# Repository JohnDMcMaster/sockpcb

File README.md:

# sockext

Chip socket extension cable adapters.
They are primarily intended to be high quality fixtures for invasive chip analysis such as microprobing, laser fault injection, and EM SCA.

Example: BP Microsystems programmers are high quality but physically large.
Unfortunately this large size precludes it from being used to read out a chip on my probe station.
Solution: extend the socket from the programmer via ribbon cable to an adapter board on the probe station (dipext-pin + dipext-sock + cable).

Projects:
  * dipext-sock: converts an IDC connector to a ZIF40 socket. Also adds patch connections
  * dipext-pin: converts DIP40 pins into an IDC connector. Also adds patch connections
  * dipext-pin-r: like above but flips pins for backside analysis
    * WARNING: not updated for new pin order
  * dipspy: patch a chip similar to dipext-sock + dipext-pin w/o cables and such
    * FIXME: needs rev to use SMD to make solder easier

IMPORTANT: pin order was swapped at this rev to match crimp connectors:
  * dipext-sock_r3
  * dipext-pin_r6
  * WARNING: dipext-pin-r_r1 is not compatible / updated yet

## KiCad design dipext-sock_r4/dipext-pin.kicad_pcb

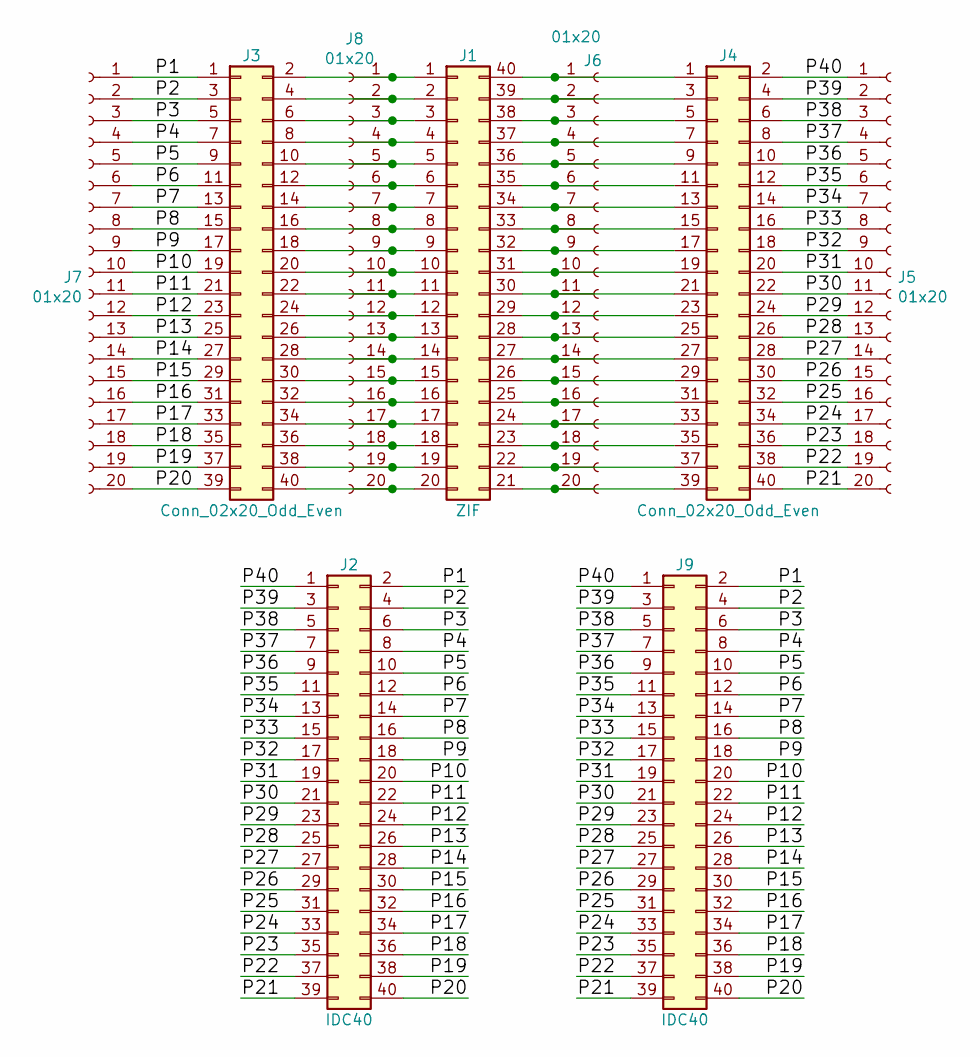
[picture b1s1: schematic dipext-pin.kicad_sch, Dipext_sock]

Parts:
J1: ZIF; mydip40
J2, J9: IDC40; IDC-Header_2x20_P2.54mm_Latch_Vertical
J3, J4: Conn_02x20_Odd_Even; Pin_Header_Straight_2x20_Pitch2.54mm
J5, J6, J7, J8: 01x20; PinHeader_1x20_P2.54mm_Vertical

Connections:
/P1: J2.2, J3.1, J7.1, J9.2
/P2: J2.4, J3.3, J7.2, J9.4
/P3: J2.6, J3.5, J7.3, J9.6
/P4: J2.8, J3.7, J7.4, J9.8
/P5: J2.10, J3.9, J7.5, J9.10
/P6: J2.12, J3.11, J7.6, J9.12
/P7: J2.14, J3.13, J7.7, J9.14
/P8: J2.16, J3.15, J7.8, J9.16
/P9: J2.18, J3.17, J7.9, J9.18
/P10: J2.20, J3.19, J7.10, J9.20
/P11: J2.22, J3.21, J7.11, J9.22
/P12: J2.24, J3.23, J7.12, J9.24
/P13: J2.26, J3.25, J7.13, J9.26
/P14: J2.28, J3.27, J7.14, J9.28
/P15: J2.30, J3.29, J7.15, J9.30
/P16: J2.32, J3.31, J7.16, J9.32
/P17: J2.34, J3.33, J7.17, J9.34
/P18: J2.36, J3.35, J7.18, J9.36
/P19: J2.38, J3.37, J7.19, J9.38
/P20: J2.40, J3.39, J7.20, J9.40
/P21: J2.39, J4.40, J5.20, J9.39
/P22: J2.37, J4.38, J5.19, J9.37
/P23: J2.35, J4.36, J5.18, J9.35
/P24: J2.33, J4.34, J5.17, J9.33
/P25: J2.31, J4.32, J5.16, J9.31
/P26: J2.29, J4.30, J5.15, J9.29
/P27: J2.27, J4.28, J5.14, J9.27
/P28: J2.25, J4.26, J5.13, J9.25
/P29: J2.23, J4.24, J5.12, J9.23
/P30: J2.21, J4.22, J5.11, J9.21
/P31: J2.19, J4.20, J5.10, J9.19
/P32: J2.17, J4.18, J5.9, J9.17
/P33: J2.15, J4.16, J5.8, J9.15
/P34: J2.13, J4.14, J5.7, J9.13
/P35: J2.11, J4.12, J5.6, J9.11
/P36: J2.9, J4.10, J5.5, J9.9
/P37: J2.7, J4.8, J5.4, J9.7
/P38: J2.5, J4.6, J5.3, J9.5
/P39: J2.3, J4.4, J5.2, J9.3
/P40: J2.1, J4.2, J5.1, J9.1
unnamed: J1.1, J3.2, J8.1
unnamed: J1.2, J3.4, J8.2
unnamed: J1.3, J3.6, J8.3
unnamed: J1.4, J3.8, J8.4
unnamed: J1.5, J3.10, J8.5
unnamed: J1.6, J3.12, J8.6
unnamed: J1.7, J3.14, J8.7
unnamed: J1.8, J3.16, J8.8
unnamed: J1.9, J3.18, J8.9
unnamed: J1.10, J3.20, J8.10
unnamed: J1.11, J3.22, J8.11
unnamed: J1.12, J3.24, J8.12
unnamed: J1.13, J3.26, J8.13
unnamed: J1.14, J3.28, J8.14
unnamed: J1.15, J3.30, J8.15
unnamed: J1.16, J3.32, J8.16
unnamed: J1.17, J3.34, J8.17
unnamed: J1.18, J3.36, J8.18
unnamed: J1.19, J3.38, J8.19
unnamed: J1.20, J3.40, J8.20
unnamed: J1.21, J4.39, J6.20
unnamed: J1.22, J4.37, J6.19
unnamed: J1.23, J4.35, J6.18
unnamed: J1.24, J4.33, J6.17
unnamed: J1.25, J4.31, J6.16
unnamed: J1.26, J4.29, J6.15
unnamed: J1.27, J4.27, J6.14
unnamed: J1.28, J4.25, J6.13
unnamed: J1.29, J4.23, J6.12
unnamed: J1.30, J4.21, J6.11
unnamed: J1.31, J4.19, J6.10
unnamed: J1.32, J4.17, J6.9
unnamed: J1.33, J4.15, J6.8
unnamed: J1.34, J4.13, J6.7
unnamed: J1.35, J4.11, J6.6
unnamed: J1.36, J4.9, J6.5
unnamed: J1.37, J4.7, J6.4
unnamed: J1.38, J4.5, J6.3
unnamed: J1.39, J4.3, J6.2
unnamed: J1.40, J4.1, J6.1

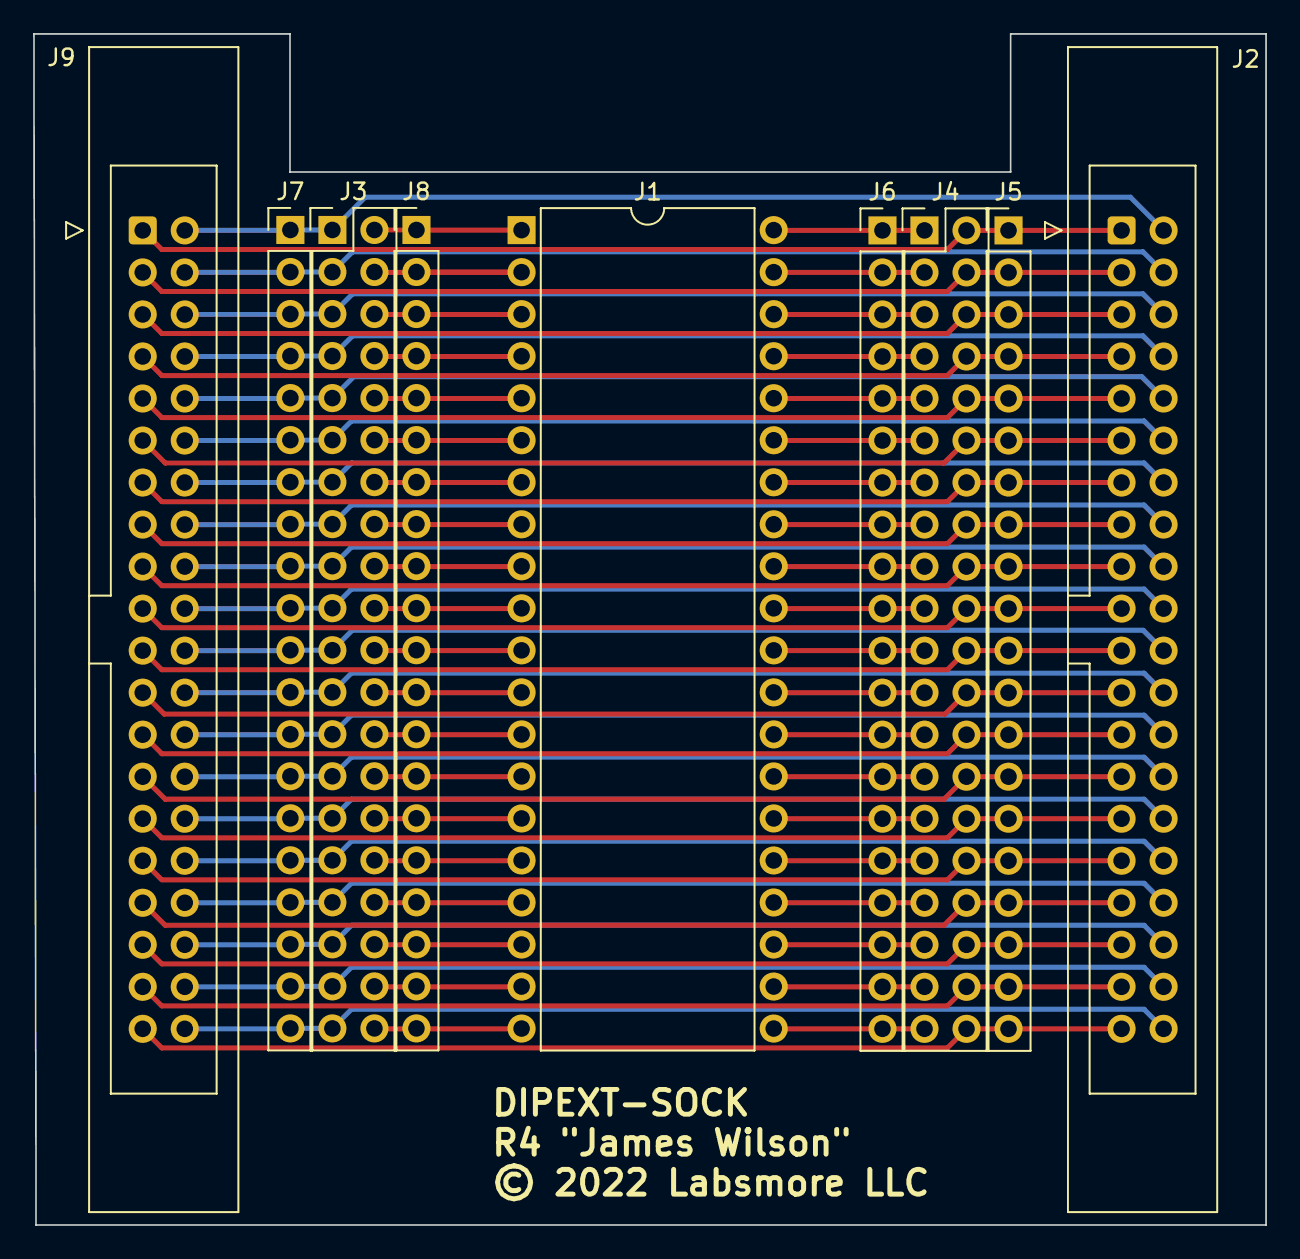
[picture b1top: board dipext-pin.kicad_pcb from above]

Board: 2 copper layers, 74.5 x 72.0 mm, 9 parts (0 on the bottom side), 80 nets.

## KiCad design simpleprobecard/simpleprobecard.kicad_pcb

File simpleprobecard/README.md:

# Simple microprobing breakout thing for 0.5mm wide probes
Hole is parametric, can be cut to any size.
Mounting points are on a standard 1" grid.

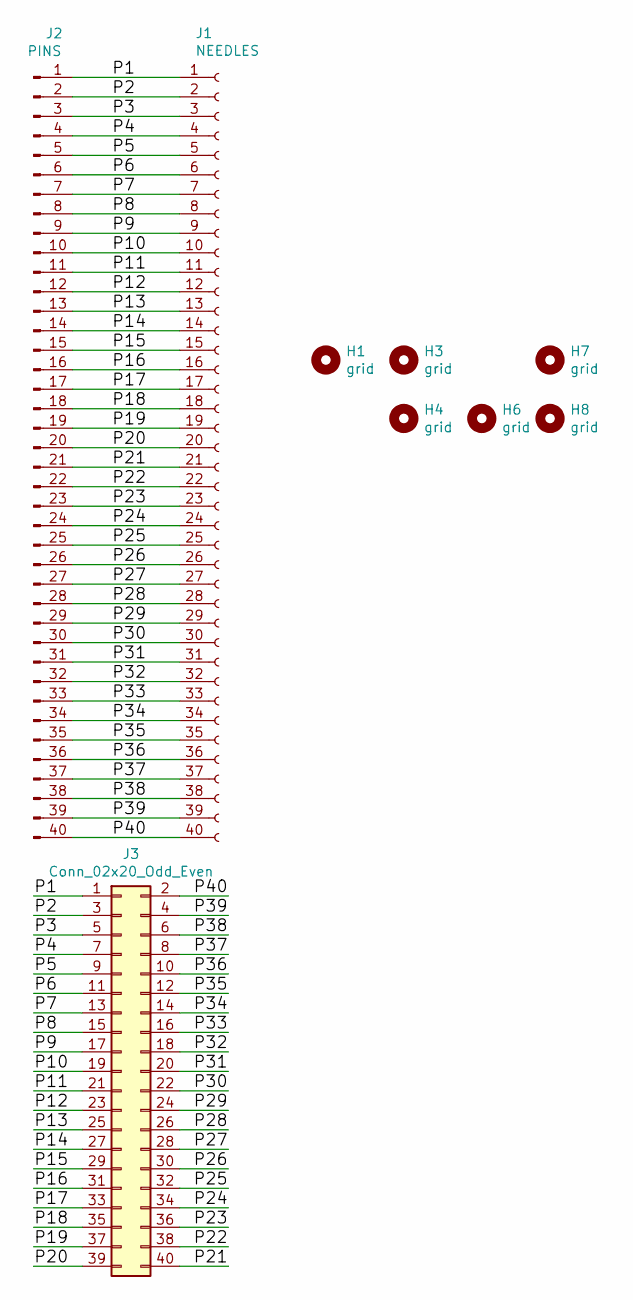
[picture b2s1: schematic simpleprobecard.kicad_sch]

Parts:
H1, H3, H4, H6, H7, H8: grid; MountingHole_4.3mm_M4_Pad_Via
J1: NEEDLES; Pin
J2: PINS; IDC-Header_2x20_P2.54mm_Latch_Vertical
J3: Conn_02x20_Odd_Even; IDC-Header_2x20_P2.54mm_Latch_Vertical

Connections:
/P1: J1.1, J2.1, J3.1
/P2: J1.2, J2.2, J3.3
/P3: J1.3, J2.3, J3.5
/P4: J1.4, J2.4, J3.7
/P5: J1.5, J2.5, J3.9
/P6: J1.6, J2.6, J3.11
/P7: J1.7, J2.7, J3.13
/P8: J1.8, J2.8, J3.15
/P9: J1.9, J2.9, J3.17
/P10: J1.10, J2.10, J3.19
/P11: J1.11, J2.11, J3.21
/P12: J1.12, J2.12, J3.23
/P13: J1.13, J2.13, J3.25
/P14: J1.14, J2.14, J3.27
/P15: J1.15, J2.15, J3.29
/P16: J1.16, J2.16, J3.31
/P17: J1.17, J2.17, J3.33
/P18: J1.18, J2.18, J3.35
/P19: J1.19, J2.19, J3.37
/P20: J1.20, J2.20, J3.39
/P21: J1.21, J2.21, J3.40
/P22: J1.22, J2.22, J3.38
/P23: J1.23, J2.23, J3.36
/P24: J1.24, J2.24, J3.34
/P25: J1.25, J2.25, J3.32
/P26: J1.26, J2.26, J3.30
/P27: J1.27, J2.27, J3.28
/P28: J1.28, J2.28, J3.26
/P29: J1.29, J2.29, J3.24
/P30: J1.30, J2.30, J3.22
/P31: J1.31, J2.31, J3.20
/P32: J1.32, J2.32, J3.18
/P33: J1.33, J2.33, J3.16
/P34: J1.34, J2.34, J3.14
/P35: J1.35, J2.35, J3.12
/P36: J1.36, J2.36, J3.10
/P37: J1.37, J2.37, J3.8
/P38: J1.38, J2.38, J3.6
/P39: J1.39, J2.39, J3.4
/P40: J1.40, J2.40, J3.2

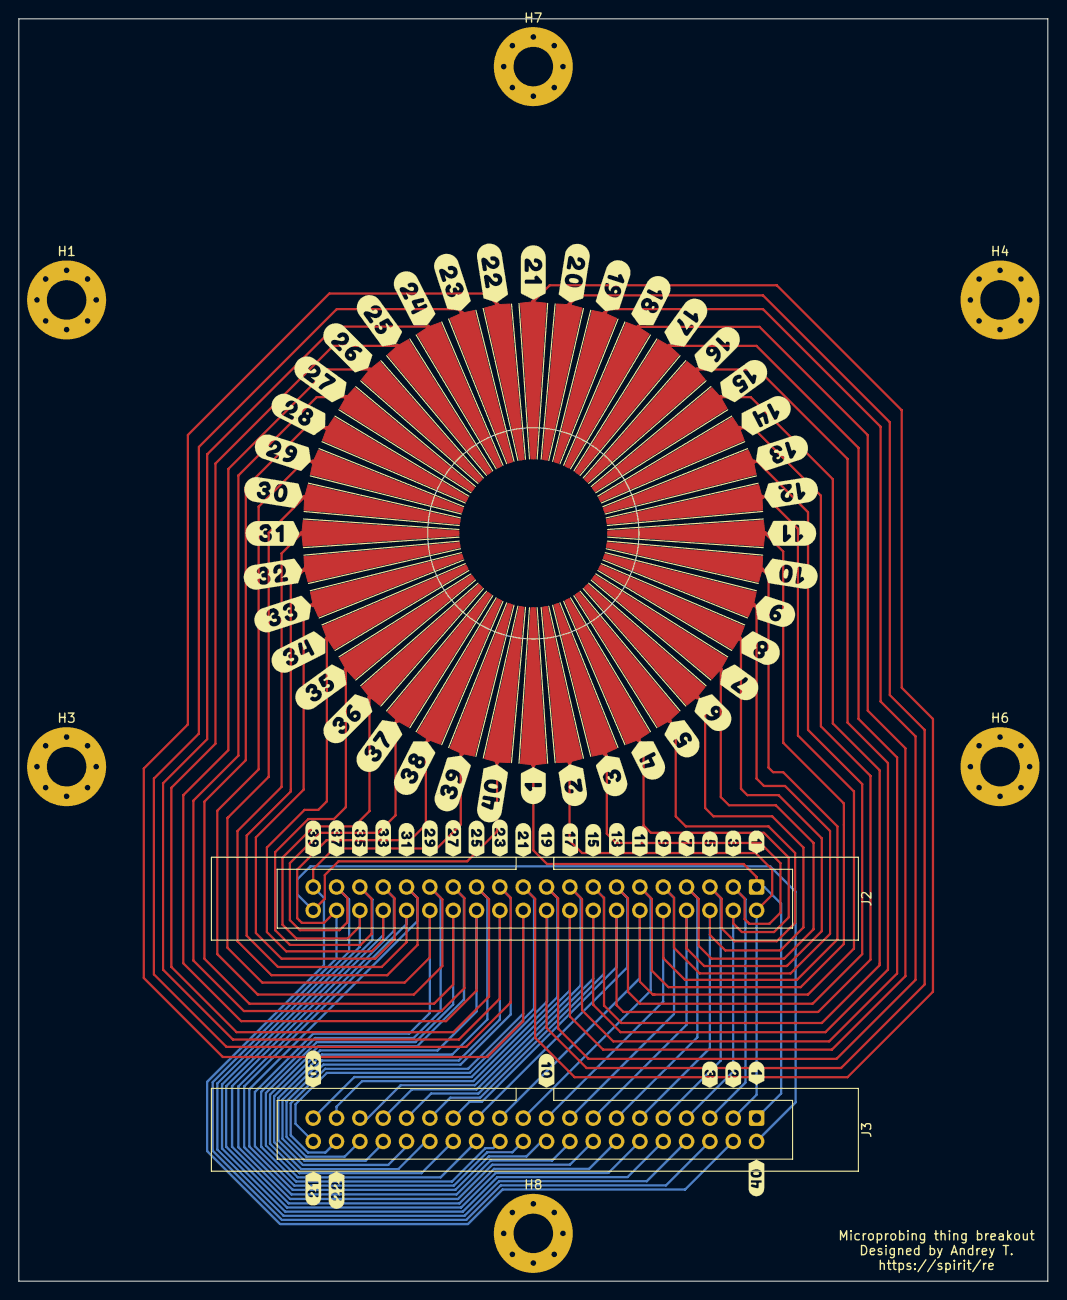
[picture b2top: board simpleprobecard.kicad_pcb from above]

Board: 2 copper layers, 112.0 x 137.4 mm, 9 parts (0 on the bottom side), 40 nets.

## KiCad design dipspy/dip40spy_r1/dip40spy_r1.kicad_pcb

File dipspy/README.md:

# dipspy
DIP40 signal parallel and series signal tap.
Usually you'll want jumpers in the center positions to connect the two sockets together.
Alternatively install a current probe, feed in an external signal, etc.
Logic analyzers can be easily attached to the extra pins

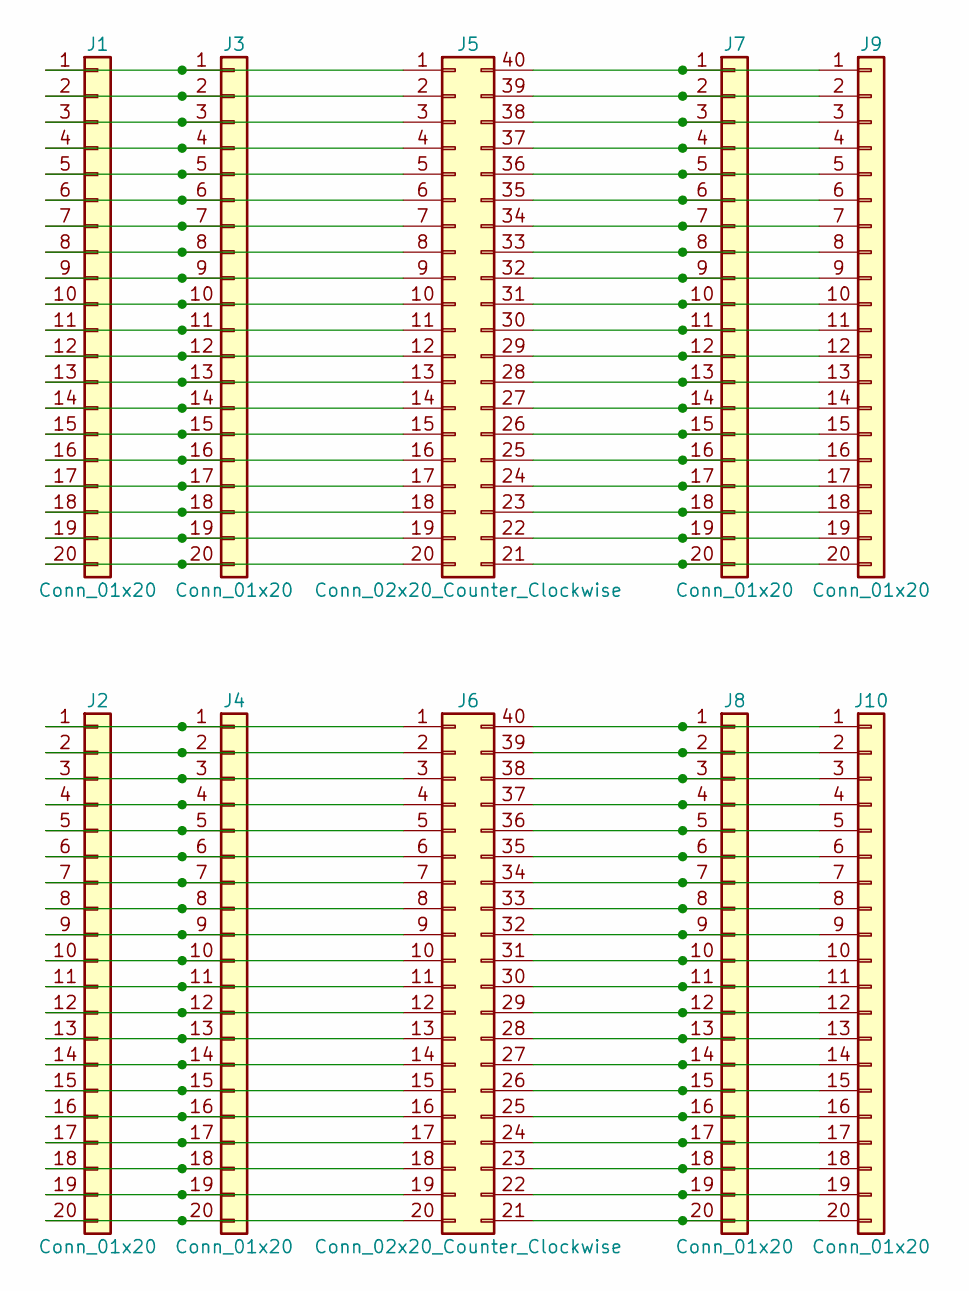
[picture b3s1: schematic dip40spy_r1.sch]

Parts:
J1, J2, J3, J4, J7, J8, J9, J10: Conn_01x20; Pin_Header_Straight_1x20_Pitch2.54mm
J5: Conn_02x20_Counter_Clockwise; aries_40-6554-10_DIP-40_W15.24mm_ZIF
J6: Conn_02x20_Counter_Clockwise; dip40-0.3

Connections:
unnamed: J1.1, J3.1, J5.1
unnamed: J1.2, J3.2, J5.2
unnamed: J1.3, J3.3, J5.3
unnamed: J1.4, J3.4, J5.4
unnamed: J1.5, J3.5, J5.5
unnamed: J1.6, J3.6, J5.6
unnamed: J1.7, J3.7, J5.7
unnamed: J1.8, J3.8, J5.8
unnamed: J1.9, J3.9, J5.9
unnamed: J1.10, J3.10, J5.10
unnamed: J1.11, J3.11, J5.11
unnamed: J1.12, J3.12, J5.12
unnamed: J1.13, J3.13, J5.13
unnamed: J1.14, J3.14, J5.14
unnamed: J1.15, J3.15, J5.15
unnamed: J1.16, J3.16, J5.16
unnamed: J1.17, J3.17, J5.17
unnamed: J1.18, J3.18, J5.18
unnamed: J1.19, J3.19, J5.19
unnamed: J1.20, J3.20, J5.20
unnamed: J2.1, J4.1, J6.1
unnamed: J2.2, J4.2, J6.2
unnamed: J2.3, J4.3, J6.3
unnamed: J2.4, J4.4, J6.4
unnamed: J2.5, J4.5, J6.5
unnamed: J2.6, J4.6, J6.6
unnamed: J2.7, J4.7, J6.7
unnamed: J2.8, J4.8, J6.8
unnamed: J2.9, J4.9, J6.9
unnamed: J2.10, J4.10, J6.10
unnamed: J2.11, J4.11, J6.11
unnamed: J2.12, J4.12, J6.12
unnamed: J2.13, J4.13, J6.13
unnamed: J2.14, J4.14, J6.14
unnamed: J2.15, J4.15, J6.15
unnamed: J2.16, J4.16, J6.16
unnamed: J2.17, J4.17, J6.17
unnamed: J2.18, J4.18, J6.18
unnamed: J2.19, J4.19, J6.19
unnamed: J2.20, J4.20, J6.20
unnamed: J5.21, J7.20, J9.20
unnamed: J5.22, J7.19, J9.19
unnamed: J5.23, J7.18, J9.18
unnamed: J5.24, J7.17, J9.17
unnamed: J5.25, J7.16, J9.16
unnamed: J5.26, J7.15, J9.15
unnamed: J5.27, J7.14, J9.14
unnamed: J5.28, J7.13, J9.13
unnamed: J5.29, J7.12, J9.12
unnamed: J5.30, J7.11, J9.11
unnamed: J5.31, J7.10, J9.10
unnamed: J5.32, J7.9, J9.9
unnamed: J5.33, J7.8, J9.8
unnamed: J5.34, J7.7, J9.7
unnamed: J5.35, J7.6, J9.6
unnamed: J5.36, J7.5, J9.5
unnamed: J5.37, J7.4, J9.4
unnamed: J5.38, J7.3, J9.3
unnamed: J5.39, J7.2, J9.2
unnamed: J5.40, J7.1, J9.1
unnamed: J6.40, J8.1, J10.1
unnamed: J6.39, J8.2, J10.2
unnamed: J6.38, J8.3, J10.3
unnamed: J6.37, J8.4, J10.4
unnamed: J6.36, J8.5, J10.5
unnamed: J6.35, J8.6, J10.6
unnamed: J6.34, J8.7, J10.7
unnamed: J6.33, J8.8, J10.8
unnamed: J6.32, J8.9, J10.9
unnamed: J6.31, J8.10, J10.10
unnamed: J6.30, J8.11, J10.11
unnamed: J6.29, J8.12, J10.12
unnamed: J6.28, J8.13, J10.13
unnamed: J6.27, J8.14, J10.14
unnamed: J6.26, J8.15, J10.15
unnamed: J6.25, J8.16, J10.16
unnamed: J6.24, J8.17, J10.17
unnamed: J6.23, J8.18, J10.18
unnamed: J6.22, J8.19, J10.19
unnamed: J6.21, J8.20, J10.20

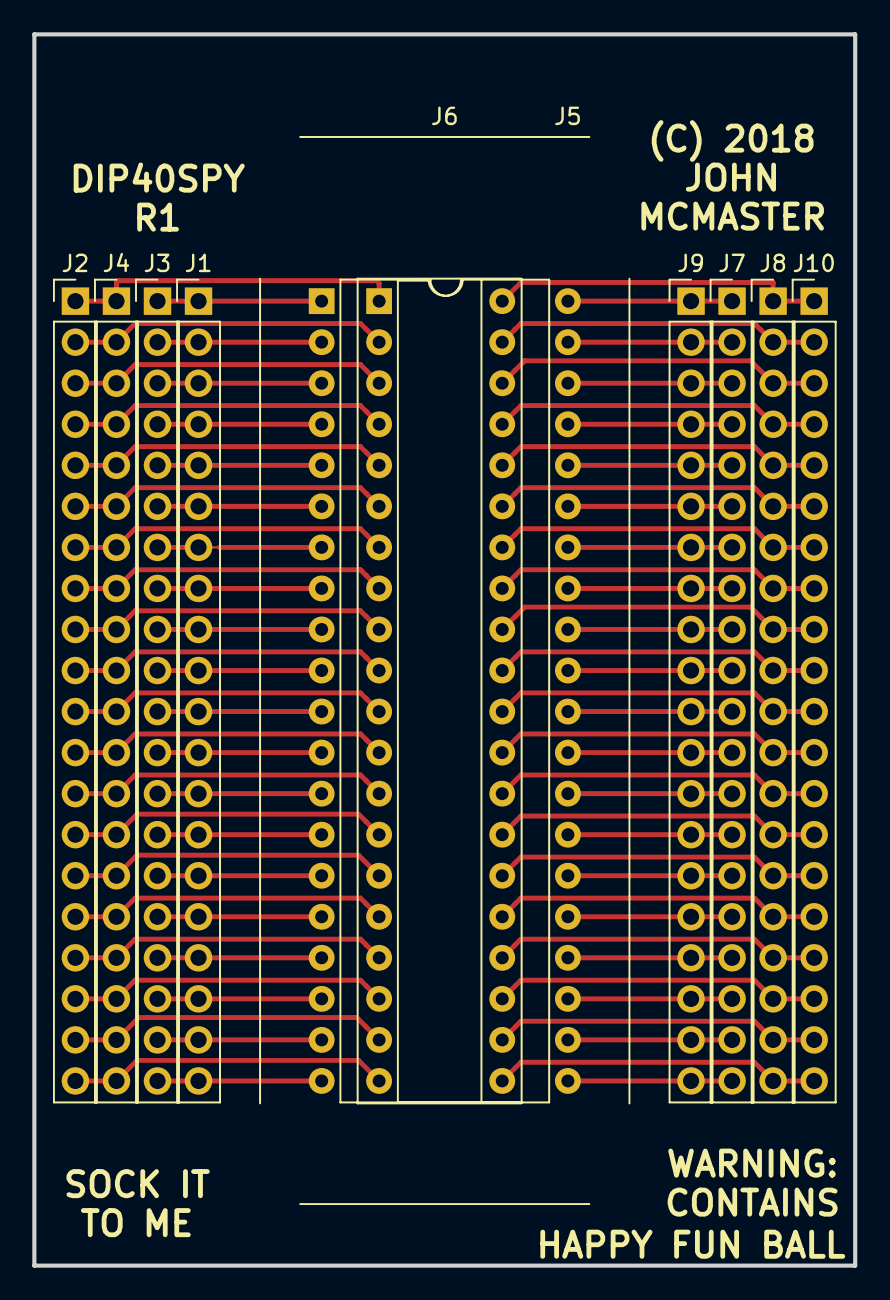
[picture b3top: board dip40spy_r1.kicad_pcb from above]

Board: 2 copper layers, 50.8 x 76.2 mm, 10 parts (0 on the bottom side), 80 nets.

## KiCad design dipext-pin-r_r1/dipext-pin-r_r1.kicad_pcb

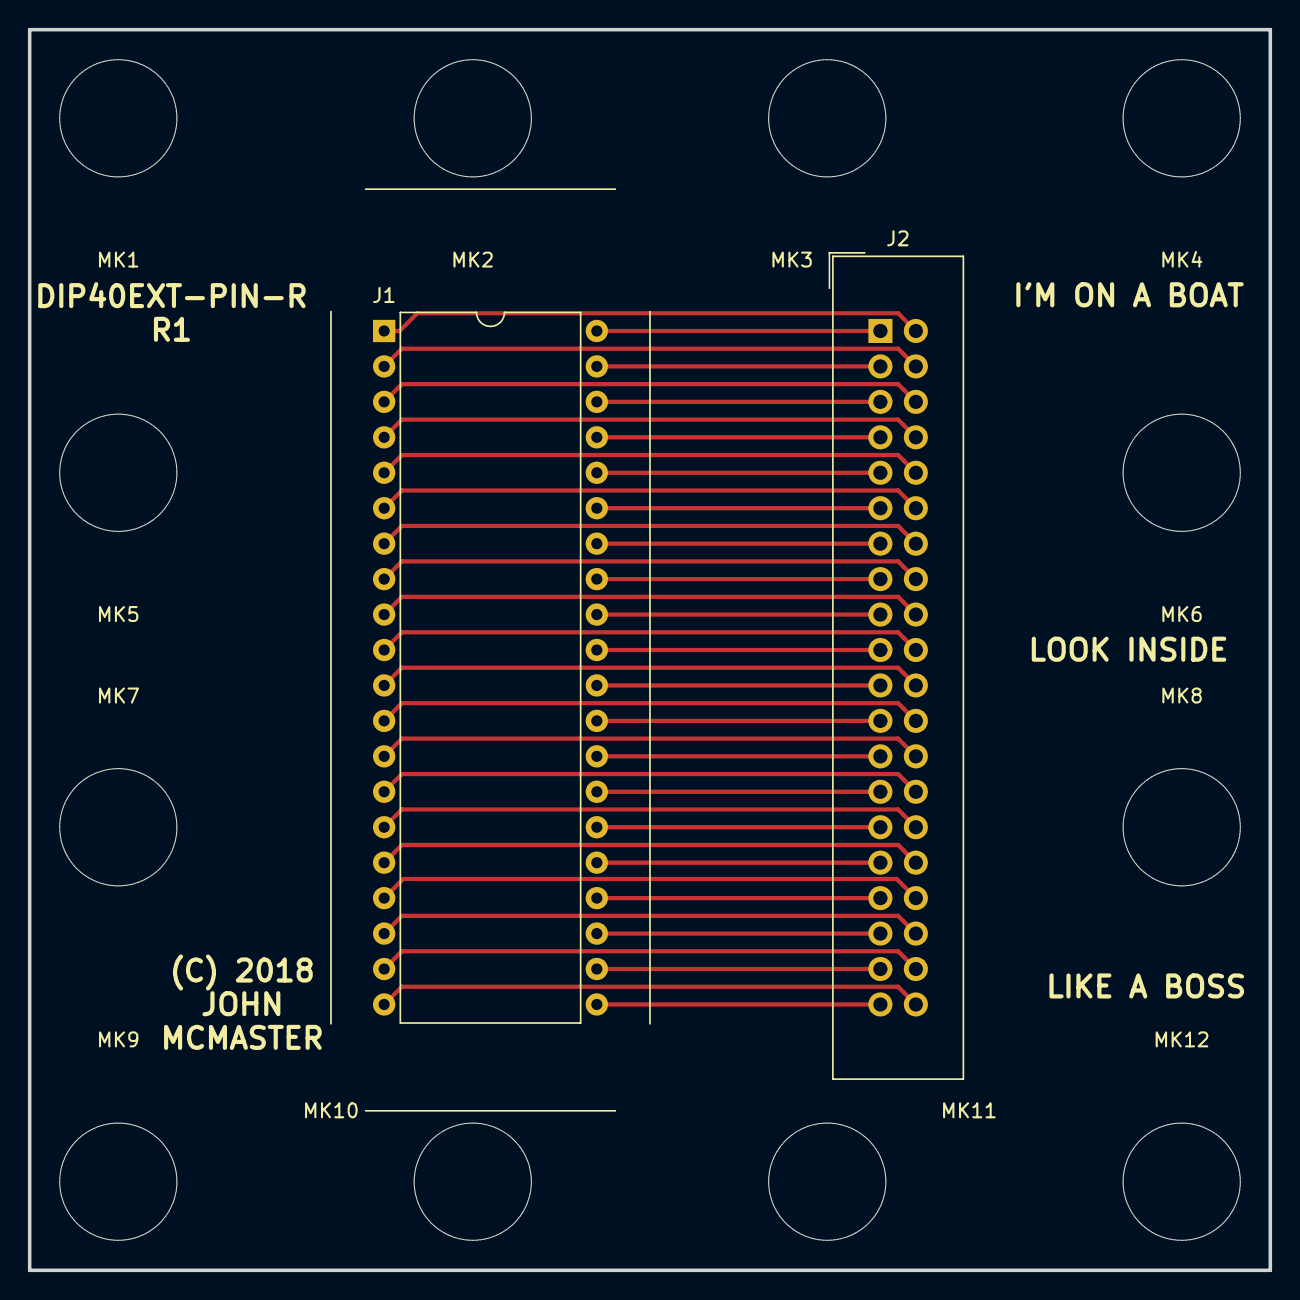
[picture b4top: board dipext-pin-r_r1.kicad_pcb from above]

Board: 2 copper layers, 88.9 x 88.9 mm, 14 parts (0 on the bottom side), 40 nets.

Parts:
J1: ZIF; aries_40-6554-10_DIP-40_W15.24mm_ZIF
J2: IDC40; IDC-Header_2x20_Pitch2.54mm_Straight
MK1, MK2, MK3, MK4, MK5, MK6, MK7, MK8, MK9, MK10, MK11, MK12: Mounting_Hole; MountingHole_8.4mm_M8

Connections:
/P1: J1.1, J2.2
/P2: J1.2, J2.4
/P3: J1.3, J2.6
/P4: J1.4, J2.8
/P5: J1.5, J2.10
/P6: J1.6, J2.12
/P7: J1.7, J2.14
/P8: J1.8, J2.16
/P9: J1.9, J2.18
/P10: J1.10, J2.20
/P11: J1.11, J2.22
/P12: J1.12, J2.24
/P13: J1.13, J2.26
/P14: J1.14, J2.28
/P15: J1.15, J2.30
/P16: J1.16, J2.32
/P17: J1.17, J2.34
/P18: J1.18, J2.36
/P19: J1.19, J2.38
/P20: J1.20, J2.40
/P21: J1.21, J2.39
/P22: J1.22, J2.37
/P23: J1.23, J2.35
/P24: J1.24, J2.33
/P25: J1.25, J2.31
/P26: J1.26, J2.29
/P27: J1.27, J2.27
/P28: J1.28, J2.25
/P29: J1.29, J2.23
/P30: J1.30, J2.21
/P31: J1.31, J2.19
/P32: J1.32, J2.17
/P33: J1.33, J2.15
/P34: J1.34, J2.13
/P35: J1.35, J2.11
/P36: J1.36, J2.9
/P37: J1.37, J2.7
/P38: J1.38, J2.5
/P39: J1.39, J2.3
/P40: J1.40, J2.1

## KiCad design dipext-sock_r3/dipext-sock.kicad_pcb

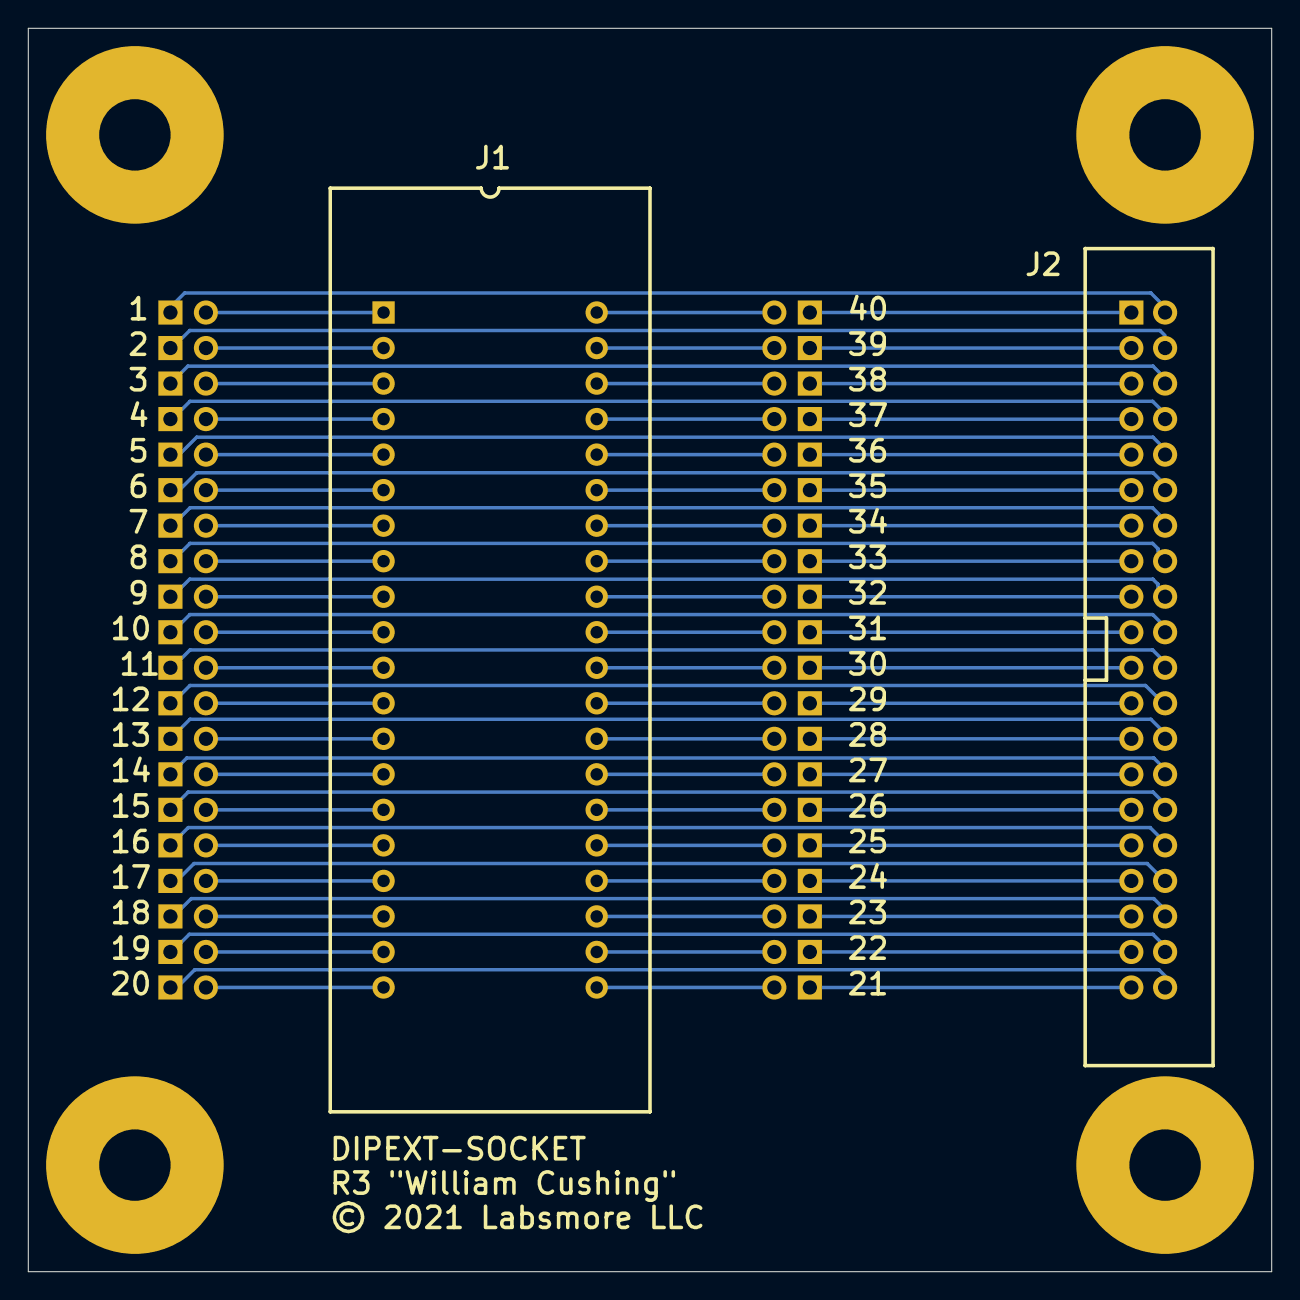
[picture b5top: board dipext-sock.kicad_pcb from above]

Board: 2 copper layers, 88.9 x 88.9 mm, 46 parts (0 on the bottom side), 80 nets.

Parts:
1, 2, 3, 4, 5, 6, 7, 8, 9, 10, 11, 12, 13, 14, 15, 16, 17, 18, 19, 20, 21, 22, 23, 24, 25, 26, 27, 28, 29, 30, 31, 32, 33, 34, 35, 36, 37, 38, 39, 40: XG4H-5031; SIL2
Designator2, Designator3, Designator4, Designator5: Comment; _buffer_ad_dipext-sock_r1_PcbLib1.PcbLib_SAE10_LOOSE
J1: 240-1288-00-0602J; 240-1300-00-0602J
J2: IDC40

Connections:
I1: 1.1, J2.1
I2: 2.1, J2.3
I3: 3.1, J2.5
I4: 4.1, J2.7
I5: 5.1, J2.9
I6: 6.1, J2.11
I7: 7.1, J2.13
I8: 8.1, J2.15
I9: 9.1, J2.17
I10: 10.1, J2.19
I11: 11.1, J2.21
I12: 12.1, J2.23
I13: 13.1, J2.25
I14: 14.1, J2.27
I15: 15.1, J2.29
I16: 16.1, J2.31
I17: 17.1, J2.33
I18: 18.1, J2.35
I19: 19.1, J2.37
I20: 20.1, J2.39
I21: 21.1, J2.40
I22: 22.1, J2.38
I23: 23.1, J2.36
I24: 24.1, J2.34
I25: 25.1, J2.32
I26: 26.1, J2.30
I27: 27.1, J2.28
I28: 28.1, J2.26
I29: 29.1, J2.24
I30: 30.1, J2.22
I31: 31.1, J2.20
I32: 32.1, J2.18
I33: 33.1, J2.16
I34: 34.1, J2.14
I35: 35.1, J2.12
I36: 36.1, J2.10
I37: 37.1, J2.8
I38: 38.1, J2.6
I39: 39.1, J2.4
I40: 40.1, J2.2
S1: 1.2, J1.1
S2: 2.2, J1.2
S3: 3.2, J1.3
S4: 4.2, J1.4
S5: 5.2, J1.5
S6: 6.2, J1.6
S7: 7.2, J1.7
S8: 8.2, J1.8
S9: 9.2, J1.9
S10: 10.2, J1.10
S11: 11.2, J1.11
S12: 12.2, J1.12
S13: 13.2, J1.13
S14: 14.2, J1.14
S15: 15.2, J1.15
S16: 16.2, J1.16
S17: 17.2, J1.17
S18: 18.2, J1.18
S19: 19.2, J1.19
S20: 20.2, J1.20
S21: 21.2, J1.21
S22: 22.2, J1.22
S23: 23.2, J1.23
S24: 24.2, J1.24
S25: 25.2, J1.25
S26: 26.2, J1.26
S27: 27.2, J1.27
S28: 28.2, J1.28
S29: 29.2, J1.29
S30: 30.2, J1.30
S31: 31.2, J1.31
S32: 32.2, J1.32
S33: 33.2, J1.33
S34: 34.2, J1.34
S35: 35.2, J1.35
S36: 36.2, J1.36
S37: 37.2, J1.37
S38: 38.2, J1.38
S39: 39.2, J1.39
S40: 40.2, J1.40

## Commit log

2018-08-15 dipext-pin-r_r1
2019-07-31 sync
2021-02-06 import dipspy
2021-02-06 Yes.
2021-02-06 Revert "Yes."
    This reverts commit 611ce2b3961d5ca419525b40e4a89030cbd90d7e.
    deleted: dipext-pin_r4/Gerbers.zip
    deleted: dipext-pin_r4/Gerbers/dipext-pin_r4-B_Cu.gbr
    deleted: dipext-pin_r4/Gerbers/dipext-pin_r4-B_Mask.gbr
    deleted: dipext-pin_r4/Gerbers/dipext-pin_r4-B_Silkscreen.gbr
    deleted: dipext-pin_r4/Gerbers/dipext-pin_r4-Edge_Cuts.gbr
2021-02-06 Yes 2, but now R5.
2021-02-06 2.54 pitch spacing
2021-02-07 First version of the simple microprobing board
    deleted: dipext-pin_r5/dipext-pin_r4-backups/dipext-pin_r4-2021-02-07_002243.zip
    deleted: dipext-pin_r5/dipext-pin_r4-backups/dipext-pin_r4-2021-02-07_010020.zip
    deleted: dipext-pin_r5/rescue-backup/dipext-pin_r4-2021-02-06-23-54-14.kicad_pro
    deleted: dipext-pin_r5/rescue-backup/dipext-pin_r4-2021-02-06-23-54-14.sch
    deleted: dipext-pin_r5/rescue-backup/dipext-pin_r4-cache-2021-02-06-23-54-14.lib
    new file: simpleprobecard/Gerbers.zip
2021-02-07 modified: dipext-pin_r4/dipext-pin_r4.kicad_pcb modified: dipext-pin_r4/dipext-pin_r4.kicad_prl modified: dipext-pin_r4/dipext-pin_r4.kicad_pro modified: dipext-pin_r5/dipext-pin_r4.kicad_prl modifie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
2021-08-29 Adding R6. Has swapped pins so that Pin1(ribbon)->Pin40(IDC). Some minor cleanup and fixes.
2021-09-30 dipext-pin_r6: simplify mounting holes
2021-09-30 renamve r4 suffix
2021-10-01 Adding dipext-sock_r3.
    Converted the r2 altium pcb files to kicad. Rewired the traces to match the flipping of the connections similar to the corresponding changes in dipext-pin R6. Note: had to suspend the DRC checks, sin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
2021-10-07 Recreating dipext-sock R3 from: dipext-pin R6, with new cut lines and mounting holes removed.
2021-10-07 Removing old files.
2021-10-07 Fixing schematic info block.
2021-10-10 Fixes to cut lines.
2021-10-10 readme update
2022-01-28 Adding R4. Added additional header, changed board outline

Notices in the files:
dipext-pin-r_r1/dipext-pin-r_r1.kicad_pcb:
(C) 2018
dipext-sock_r3/dipext-sock.kicad_pcb:
© 2021 Labsmore LLC
dipext-sock_r4/dipext-pin.kicad_pcb:
© 2022 Labsmore LLC
